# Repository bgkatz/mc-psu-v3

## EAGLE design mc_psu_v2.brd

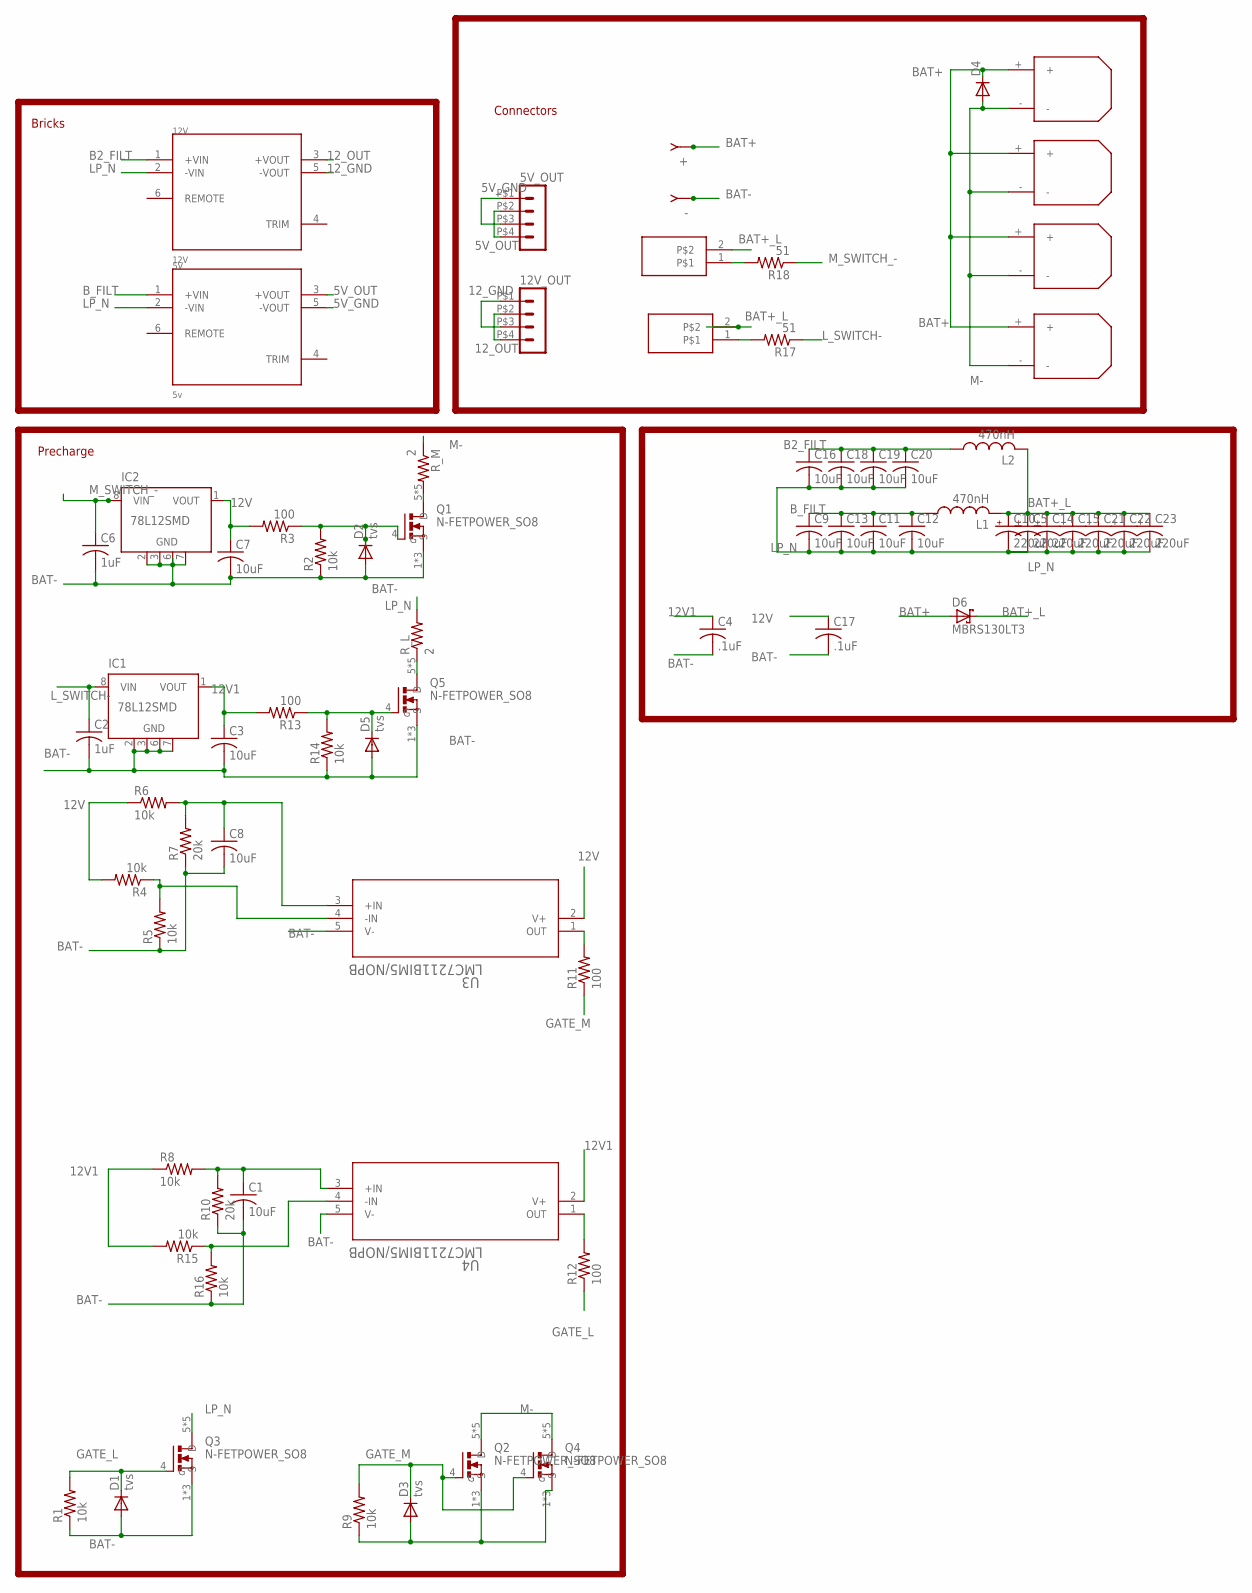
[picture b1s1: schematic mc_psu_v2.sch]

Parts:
5V: 5v; CONV_PDQ30-Q24-S5-D
5V_OUT, 12V_OUT: HEADER_POS4_43045-0401; 43045-0400
12V: 12V; CONV_PDQ30-Q24-S5-D
+: QFIT; FASTON
-: QFIT; FASTON
C1, C3, C7, C8: 10uF; C0603K
C2, C6: 1uF; C0603K
C4, C17: .1uF; C0603K
C5, C10, C14, C15, C21, C22, C23: 220uF; E3,5-8
C9, C11, C12, C13, C16, C18, C19, C20: 10uF; C1206K
D1, D2, D3, D5: tvs; DO214AC
D4: DIODE-SMB; SMB
D6: MBRS130LT3; SMB
IC1, IC2: 78L12SMD; SO08
L1, L2: 470nH; L3225P
Q1, Q2, Q3, Q4, Q5: N-FETPOWER_SO8; TRANS_TPH5900CNH,L1Q
R1, R2, R4, R5, R6, R8, R9, R14, R15, R16: 10k; R0402
R3, R11, R12, R13: 100; R0402
R7, R10: 20k; R0402
R17, R18: 51; R0603
R_L: 2; D2PAK
R_M: 2; D2PAK
U3, U4: LMC7211BIM5/NOPB; MF05A
U$3, U$8, U$9, U$10: XT30FEMALW; XT30_H_F
U$13, U$14: 2-PINM80_H; M80-840242

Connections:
5V_GND: 5V.5 (-VOUT), 5V_OUT.P$1 (1), 5V_OUT.P$3 (3)
5V_OUT: 5V.3 (+VOUT), 5V_OUT.P$2 (2), 5V_OUT.P$4 (4)
12V: C7.1, C17.1, IC2.1 (VOUT), R3.2, R4.2, R6.1, U3.2 (V+)
12V1: C3.1, C4.1, IC1.1 (VOUT), R8.1, R13.2, R15.2, U4.2 (V+)
12_GND: 12V.5 (-VOUT), 12V_OUT.P$1 (1), 12V_OUT.P$3 (3)
12_OUT: 12V.3 (+VOUT), 12V_OUT.P$2 (2), 12V_OUT.P$4 (4)
B2_FILT: 12V.1 (+VIN), C16.1, C18.1, C19.1, C20.1, L2.1
BAT+: +.1, +.2, D4.C, D6.A, U$3.+, U$8.+, U$9.+, U$10.+
BAT+_L: C5.+, C10.+, C14.+, C15.+, C21.+, C22.+, C23.+, D6.C, L1.2, L2.2, U$13.2, U$14.2
BAT-: -.1, -.2, C1.2, C2.2, C3.2, C4.2, C6.2, C7.2, C8.2, C17.2, D1.A, D2.A, D3.A, D5.A, IC1.2 (GND), IC1.3 (GND), IC1.6 (GND), IC1.7 (GND), IC2.2 (GND), IC2.3 (GND), IC2.6 (GND), IC2.7 (GND), Q1.1 (S), Q1.2 (S), Q1.3 (S), Q2.1 (S), Q2.2 (S), Q2.3 (S), Q3.1 (S), Q3.2 (S), Q3.3 (S), Q4.1 (S), Q4.2 (S), Q4.3 (S), Q5.1 (S), Q5.2 (S), Q5.3 (S), R1.1, R2.1, R5.1, R7.1, R9.1, R10.1, R14.1, R16.1, U3.5 (V-), U4.5 (V-)
B_FILT: 5V.1 (+VIN), C9.1, C11.1, C12.1, C13.1, L1.1
GATE_L: D1.C, Q3.4 (G), R1.2, R12.1
GATE_M: D3.C, Q2.4 (G), Q4.4 (G), R9.2, R11.1
LP_N: 5V.2 (-VIN), 12V.2 (-VIN), C5.-, C9.2, C10.-, C11.2, C12.2, C13.2, C14.-, C15.-, C16.2, C18.2, C19.2, C20.2, C21.-, C22.-, C23.-, Q3.5 (D), Q3.6 (D), Q3.7 (D), Q3.8 (D), Q3.EP (D), R_L.3 (2)
L_SWITCH-: C2.1, IC1.8 (VIN), R17.1
M-: D4.A, Q2.5 (D), Q2.6 (D), Q2.7 (D), Q2.8 (D), Q2.EP (D), Q4.5 (D), Q4.6 (D), Q4.7 (D), Q4.8 (D), Q4.EP (D), R_M.1, U$3.-, U$8.-, U$9.-, U$10.-
M_SWITCH_-: C6.1, IC2.8 (VIN), R18.1
unnamed: Q1.5 (D), Q1.6 (D), Q1.7 (D), Q1.8 (D), Q1.EP (D), R_M.3 (2)
unnamed: D5.C, Q5.4 (G), R13.1, R14.2
unnamed: D2.C, Q1.4 (G), R2.2, R3.1
unnamed: R12.2, U4.1 (OUT)
unnamed: R18.2, U$13.1
unnamed: C1.1, R8.2, R10.2, U4.3 (+IN)
unnamed: C8.1, R6.2, R7.2, U3.3 (+IN)
unnamed: R17.2, U$14.1
unnamed: R11.2, U3.1 (OUT)
unnamed: R4.1, R5.2, U3.4 (-IN)
unnamed: Q5.5 (D), Q5.6 (D), Q5.7 (D), Q5.8 (D), Q5.EP (D), R_L.1
unnamed: R15.1, R16.2, U4.4 (-IN)

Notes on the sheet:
Bricks
Precharge
Connectors

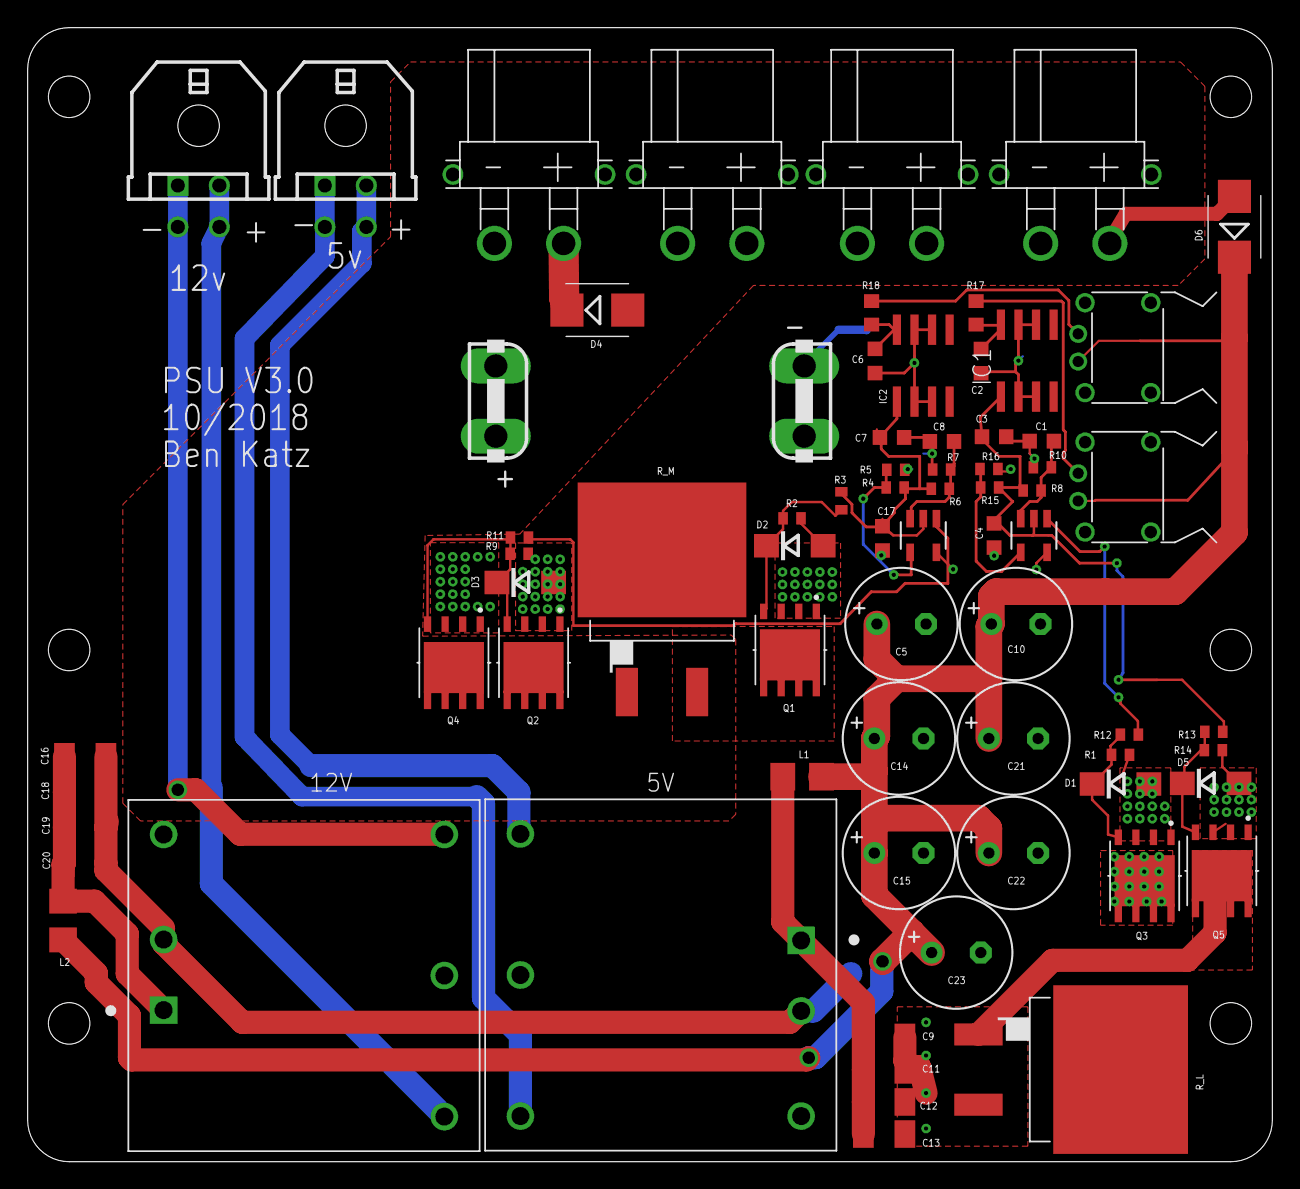
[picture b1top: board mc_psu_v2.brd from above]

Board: 2 copper layers, 90.0 x 82.0 mm, 72 parts (0 on the bottom side), 29 nets.

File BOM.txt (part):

Partlist exported from C:/Users/ben/Documents/eagle/mc_psu_v3/mc_psu_v3_share/mc_psu_v2.sch at 10/10/2019 8:51 AM

Qty Value            Device                 Package              Parts                                     Description                                                                         CUI_PURCHASE_URL                                                                                                                              DESCRIPTION                                                              DIGI-KEY_PART_NUMBER DIGI-KEY_PURCHASE_URL                                                                                                                             MANUFACTURER_PART_NUMBER MATERIAL MF  MP             PACKAGE   VENDOR           
1                    DIODE-SMB              SMB                  D4                                        DIODE                                                                                                                                                                                                                                                                                                                                                                                                                                                                                                                                                             
2                    HEADER_POS4_43045-0401 43045-0400           5V_OUT, 12V_OUT                           Molex - Micro-Fit 3.0 Series connector,  3.00mm (0.118") pitch header, 4 positions.                                                                                                                                                                                                                                                                                                                                                                                                                                                                               
2   .1uF             C-USC0603K             C0603K               C4, C17                                   CAPACITOR, American symbol                                                                                                                                                                                                                                                                                                                                                                                                                                                                                                                                        
4   100              R-US_R0402             R0402                R3, R11, R12, R13                         RESISTOR, American symbol                                                                                                                                                                                                                                                                                                                                                                                                                                                                                                                                         
10  10k              R-US_R0402             R0402                R1, R2, R4, R5, R6, R8, R9, R14, R15, R16 RESISTOR, American symbol                                                                                                                                                                                                                                                                                                                                                                                                                                                                                                                                         
4   10uF             C-USC0603K             C0603K               C1, C3, C7, C8                            CAPACITOR, American symbol                                                                                                                                                                                                                                                                                                                                                                                                                                                                                                                                        
8   10uF             C-USC1206K             C1206K               C9, C11, C12, C13, C16, C18, C19, C20     CAPACITOR, American symbol                                                                                                                                                                                                                                                                                                                                                                                                                                                                                                                                        
1   12V              PDQ30-Q24-S5-D         CONV_PDQ30-Q24-S5-D  12V                                       12 Vdc, 2.5 A, 30 W, 9 ~ 36 Vdc                                                     https://www.cui.com/product/power/dc-dc-converters/isolated/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  PDQ30-D Series 30 W 6 A 24 V Input 5 V Output Isolated DC-DC Converter  102-3891-ND          https://www.digikey.com/product-detail/en/cui-inc/PDQ30-Q24-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                                   CUI PDQ30-Q24-S5-D DIP-6 CUI                  
2   1uF              C-USC0603K             C0603K               C2, C6                                    CAPACITOR, American symbol                                                                                                                                                                                                                                                                                                                                                                                                                                                                                                                                        
2   2-PINM80_H       2-PINM80_H             M80-840242           U$13, U$14                                                                                                                                                                                                                                                                                                                                                                                                                                                                                                                                                                                                  
2   20k              R-US_R0402             R0402                R7, R10                                   RESISTOR, American symbol                                                                                                                                                                                                                                                                                                                                                                                                                                                                                                                                         
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
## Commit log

2020-08-04 committing everything
